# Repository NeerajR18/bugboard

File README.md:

# bugboard
STM32 Based Development Board

Note : - This is still a work in progress.

bugboard is a development board with the STM32G431CBT6 as its core. 

This development board is intended to be used in a keyboard PCB. 

# Features

- STM32G431CBT6
- Built-in USB-C Port
- Small size design

# What is a development board?

A development board is a PCB (Printed Circuit Board) with an MCU along with other components such as a USB port, crystals etc. to make prototyping and designing circuits easier.
Since it already has certain components, it can be used directly in many circuits to save cost as well as time.
Development boards can vary in size, components, MCU type, amount of GPIOs etc.

bugboard, has the STM32G431CBT6 as its MCU and was made to be used in a PCB as well as a personal project to learn how to make bigger circuits for me.

# PCB

- Schematic

- PCB

Front

Back

# Images

Blender render of the PCB

This project was made using-
- KiCad
- Blender

# Bill Of Materials
|Item                    |Qty. |Price (USD)|Ext. (USD)|Link                                                                                                                              |
|------------------------|-----|-----------|----------|----------------------------------------------------------------------------------------------------------------------------------|
| C529355                |  1  |  3.0856   | 3.09     | https://www.lcsc.com/product-detail/C529355.html                                                                                 |
| C105872                | 100 |  0.0009   | 0.09     | https://www.lcsc.com/product-detail/C105872.html                                                                                 |
| C60490                 | 100 |  0.0008   | 0.08     | https://www.lcsc.com/product-detail/C60490                                                                                       |
| C5446                  | 5   |  0.1062   | 0.53     | https://www.lcsc.com/product-detail/C5446.html                                                                                   |
| C2765186               | 20  |  0.0617   | 1.23     | https://www.lcsc.com/product-detail/C2765186.html                                                                                |
| C5180302               | 5   |  0.0403   | 0.2      | https://www.lcsc.com/product-detail/C5180302.html                                                                                | 
| C60474                 | 100 |  0.0010   | 0.1      | https://www.lcsc.com/product-detail/C60474.html                                                                                  |
| C96446                 | 20  |  0.0181   | 0.36     | https://www.lcsc.com/product-detail/C96446.html                                                                                  |
| C37704                 | 20  |  0.0313   | 0.63     | https://www.lcsc.com/product-detail/C37704.html                                                                                  |
| C720477                | 10  |  0.056    | 0.56     | https://www.lcsc.com/product-detail/C720477.html                                                                                 |

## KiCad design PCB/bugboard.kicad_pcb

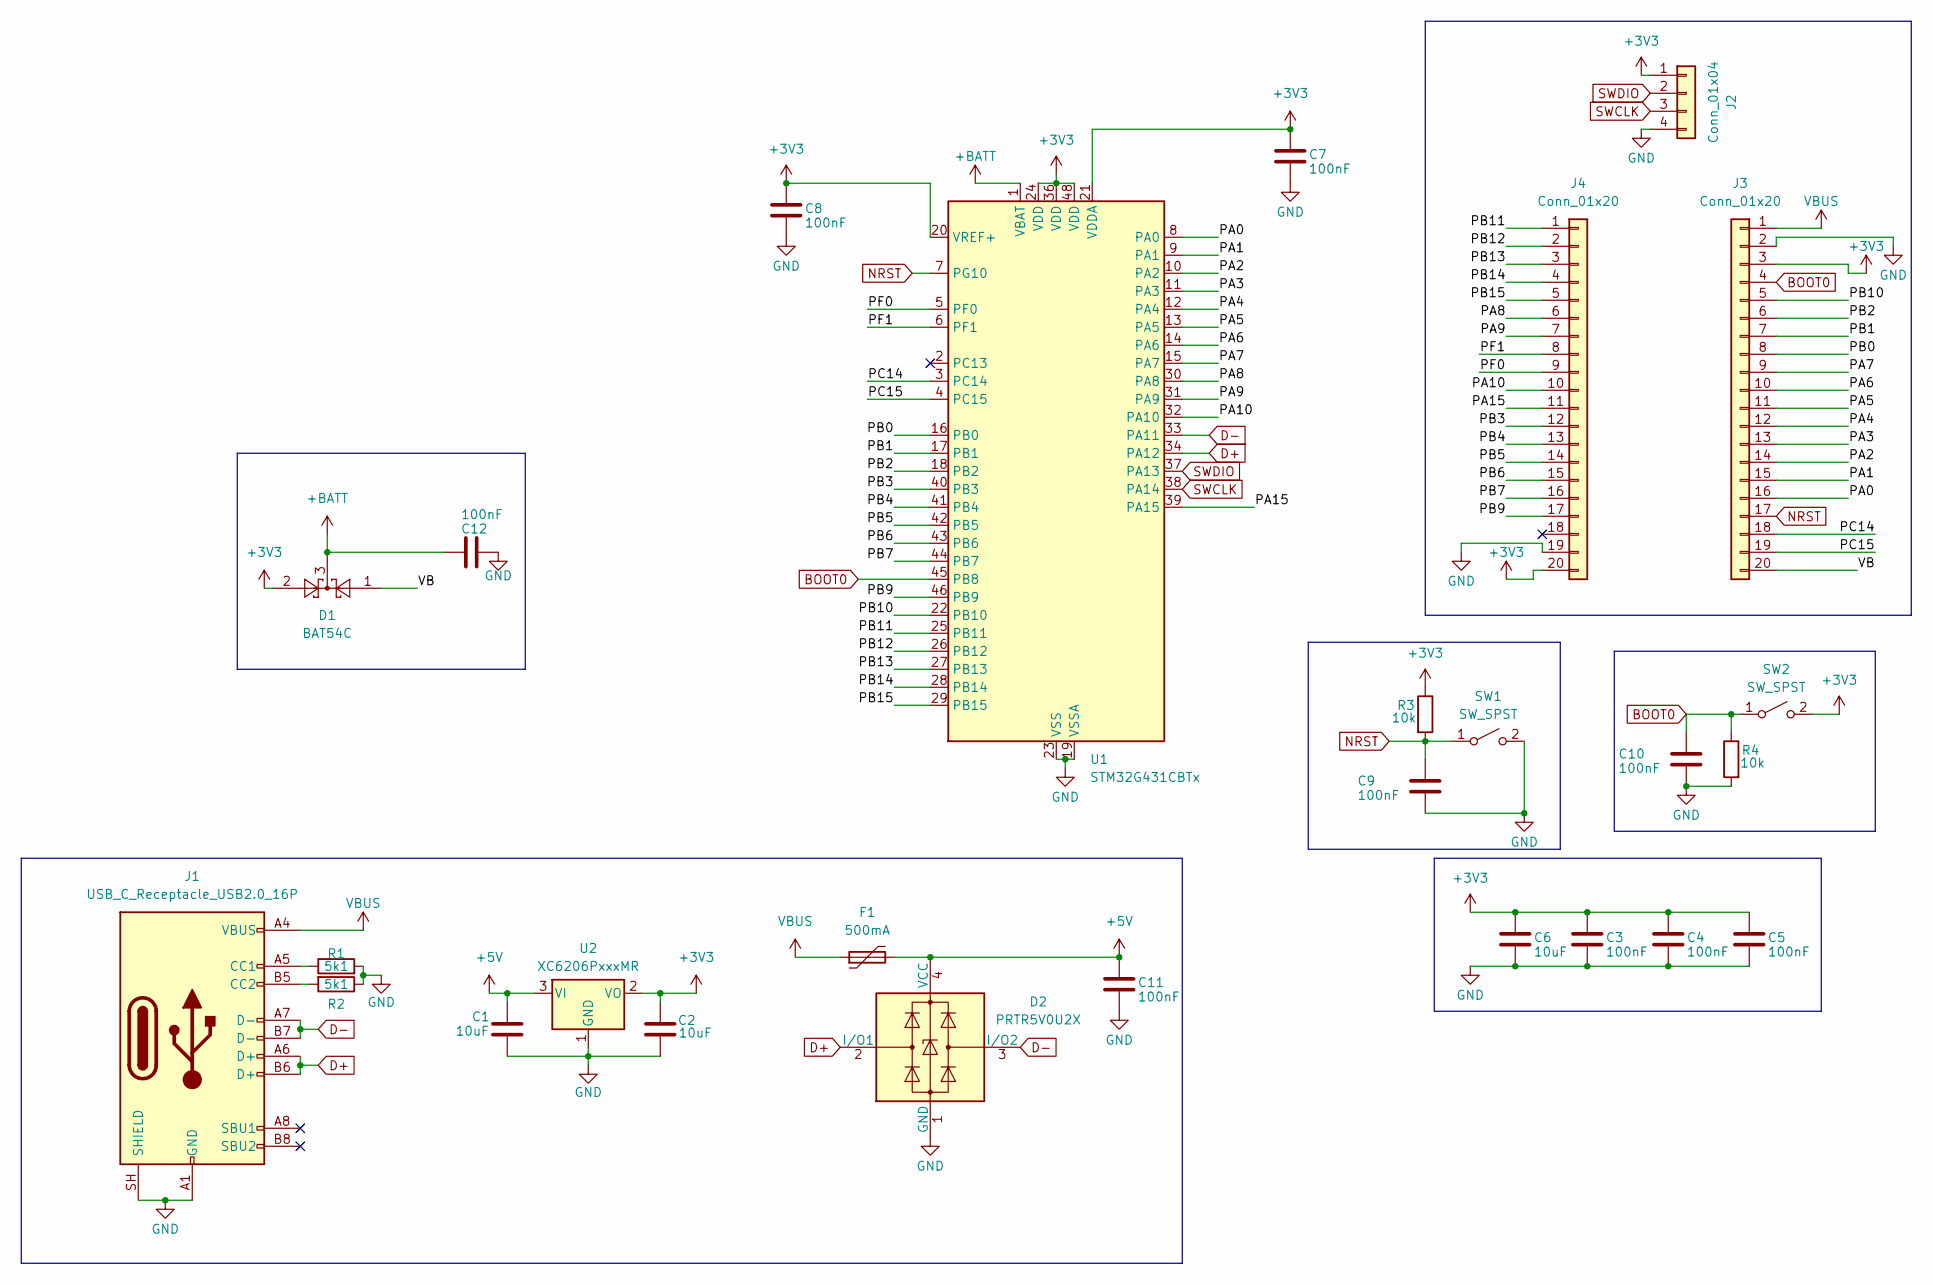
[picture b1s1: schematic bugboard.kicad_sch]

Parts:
C1, C2: 10uF; C_0402_1005Metric
C3, C4, C5, C7, C8, C9, C10, C11, C12: 100nF; C_0402_1005Metric
C6: 10uF; C_0603_1608Metric
D1: BAT54C; SOT-23
D2: PRTR5V0U2X; SOT-143
F1: 500mA; Fuse_1206_3216Metric
J1: USB_C_Receptacle_USB2.0_16P; USB_C_Receptacle_HRO_TYPE-C-31-M-12
J2: Conn_01x04; PinHeader_1x04_P2.54mm_Vertical
J3, J4: Conn_01x20; PinHeader_1x20_P2.54mm_Vertical
R1, R2: 5k1; R_0402_1005Metric
R3, R4: 10k; R_0402_1005Metric
SW1, SW2: SW_SPST; SW_SPST_TS-1088-xR020
U1: STM32G431CBTx; LQFP-48_7x7mm_P0.5mm
U2: XC6206PxxxMR; SOT-23-3

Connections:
+3V3: C2.2, C3.1, C4.1, C5.1, C6.1, C7.1, C8.1, D1.2, J2.1, J3.3, J4.20, R3.1, SW2.2 (B), U1.20 (VREF+), U1.21 (VDDA), U1.24 (VDD), U1.36 (VDD), U1.48 (VDD), U2.2 (VO)
+5V: C1.1, C11.1, D2.4 (VCC), F1.2, U2.3 (VI)
+BATT: C12.1, D1.3, U1.1 (VBAT)
/PA0: J3.16, U1.8 (PA0)
/PA1: J3.15, U1.9 (PA1)
/PA2: J3.14, U1.10 (PA2)
/PA3: J3.13, U1.11 (PA3)
/PA4: J3.12, U1.12 (PA4)
/PA5: J3.11, U1.13 (PA5)
/PA6: J3.10, U1.14 (PA6)
/PA7: J3.9, U1.15 (PA7)
/PA8: J4.6, U1.30 (PA8)
/PA9: J4.7, U1.31 (PA9)
/PA10: J4.10, U1.32 (PA10)
/PA15: J4.11, U1.39 (PA15)
/PB0: J3.8, U1.16 (PB0)
/PB1: J3.7, U1.17 (PB1)
/PB2: J3.6, U1.18 (PB2)
/PB3: J4.12, U1.40 (PB3)
/PB4: J4.13, U1.41 (PB4)
/PB5: J4.14, U1.42 (PB5)
/PB6: J4.15, U1.43 (PB6)
/PB7: J4.16, U1.44 (PB7)
/PB9: J4.17, U1.46 (PB9)
/PB10: J3.5, U1.22 (PB10)
/PB11: J4.1, U1.25 (PB11)
/PB12: J4.2, U1.26 (PB12)
/PB13: J4.3, U1.27 (PB13)
/PB14: J4.4, U1.28 (PB14)
/PB15: J4.5, U1.29 (PB15)
/PC14: J3.18, U1.3 (PC14)
/PC15: J3.19, U1.4 (PC15)
/PF0: J4.9, U1.5 (PF0)
/PF1: J4.8, U1.6 (PF1)
/VB: D1.1, J3.20
BOOT0: C10.1, J3.4, R4.1, SW2.1 (A), U1.45 (PB8); also elsewhere on the board
D+: D2.2 (I/O1), J1.A6 (D+), J1.B6 (D+), U1.34 (PA12)
D-: D2.3 (I/O2), J1.A7 (D-), J1.B7 (D-), U1.33 (PA11)
GND: C1.2, C2.1, C3.2, C4.2, C5.2, C6.2, C7.2, C8.2, C9.2, C10.2, C11.2, C12.2, D2.1 (GND), J1.A1 (GND), J1.A12 (GND), J1.B1 (GND), J1.B12 (GND), J1.SH (SHIELD), J2.4, J3.2, J4.19, R1.2, R2.1, R4.2, SW1.2 (B), U1.19 (VSSA), U1.23 (VSS), U1.35 (VSS), U1.47 (VSS), U2.1 (GND); also elsewhere on the board
NRST: C9.1, J3.17, R3.2, SW1.1 (A), U1.7 (PG10)
unnamed: J1.A5 (CC1), R1.1
unnamed: J1.B5 (CC2), R2.2
SWCLK: J2.3, U1.38 (PA14)
SWDIO: J2.2, U1.37 (PA13)
VBUS: F1.1, J1.A4 (VBUS), J1.A9 (VBUS), J1.B4 (VBUS), J1.B9 (VBUS), J3.1

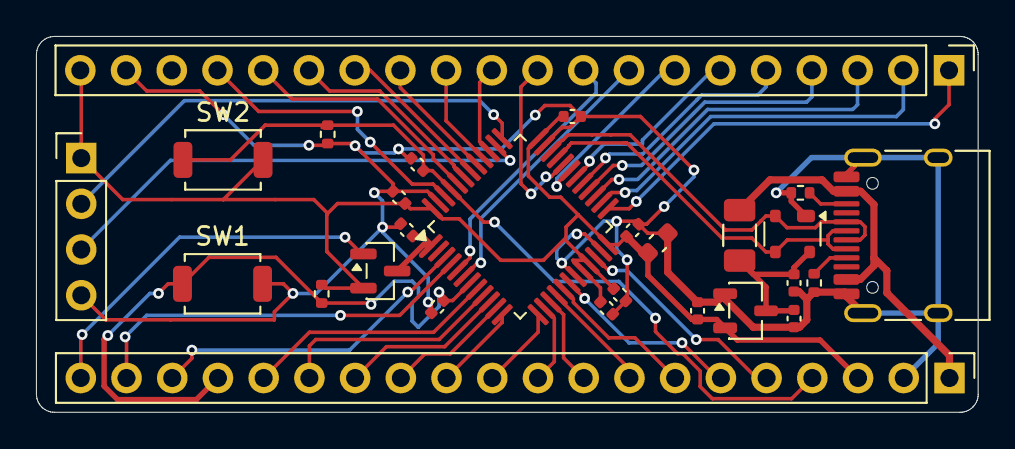
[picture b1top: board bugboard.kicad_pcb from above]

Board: 2 copper layers, 52.3 x 20.9 mm, 27 parts (0 on the bottom side), 45 nets.

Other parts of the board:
C17: 100nF; C_0402_1005Metric

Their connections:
BOOT0: C17.1; also elsewhere on the board
GND: C17.2; also elsewhere on the board

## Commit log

2026-04-18 Added PCB and Schematic
2026-04-18 Updated gerbers
2026-04-18 Added zine page to README
2026-04-18 BOM and Zine added
2026-04-19 Added pdf format of zine
2026-04-27 Add new image to README
